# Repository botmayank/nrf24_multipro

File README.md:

# nrf24_multipro_h8_pc
nRF24L01 multi-protocol RC transmitter project being used for JJRC/Eachine H8 mini to control over Serial. This project aims to develop a USB dongle to control the H8 directly from the PC using the nRF24L01+ module and later expand to control and/or charge multiple quadcopters with this custom hardware based on the Arduino Leonardo (Atmega32u4).

The main Arduino code is in the nRF24_multipro folder with the main sketch being nRF24_multipro.ino. The script to control the quad over serial is serial_test.py while the board files for the Quadstick are in the hardware_design folder.

This project is based on the work of perrystao:
https://github.com/perrytsao/nrf24_cx10_pc

which in turn is based upon the awesome nrf24_multipro project by goebish:
https://github.com/goebish/nrf24_multipro

Arduino Nano and nRF24L01+ Module on perfboard to control Syma X20

## Connections

| Arduino Uno/Nano    | NRF24L01+ Module               | nRF Pin No.   |
|---------------------|--------------------------------|---------------|
| GND                 | GND                            | 1             |
| 3.3V                | VCC                            | 2             |
| D5 (Digital 5)      | CE                             | 3             |
| A1 (Analog 1)       | CSN                            | 4             |
| D4 (Digital 4)      | SCK                            | 5             |
| D3 (Digital 3)      | MOSI                           | 6             |
| A0 (Analog 0)       | MISO                           | 7             |
| Not Used            | IRQ                            | 8             |

# Configure

run `export PYTHONPATH=.` at the root of the project folder to run the files from terminal. 
Why this isn't needed on Pycharm is because it sets it for you.

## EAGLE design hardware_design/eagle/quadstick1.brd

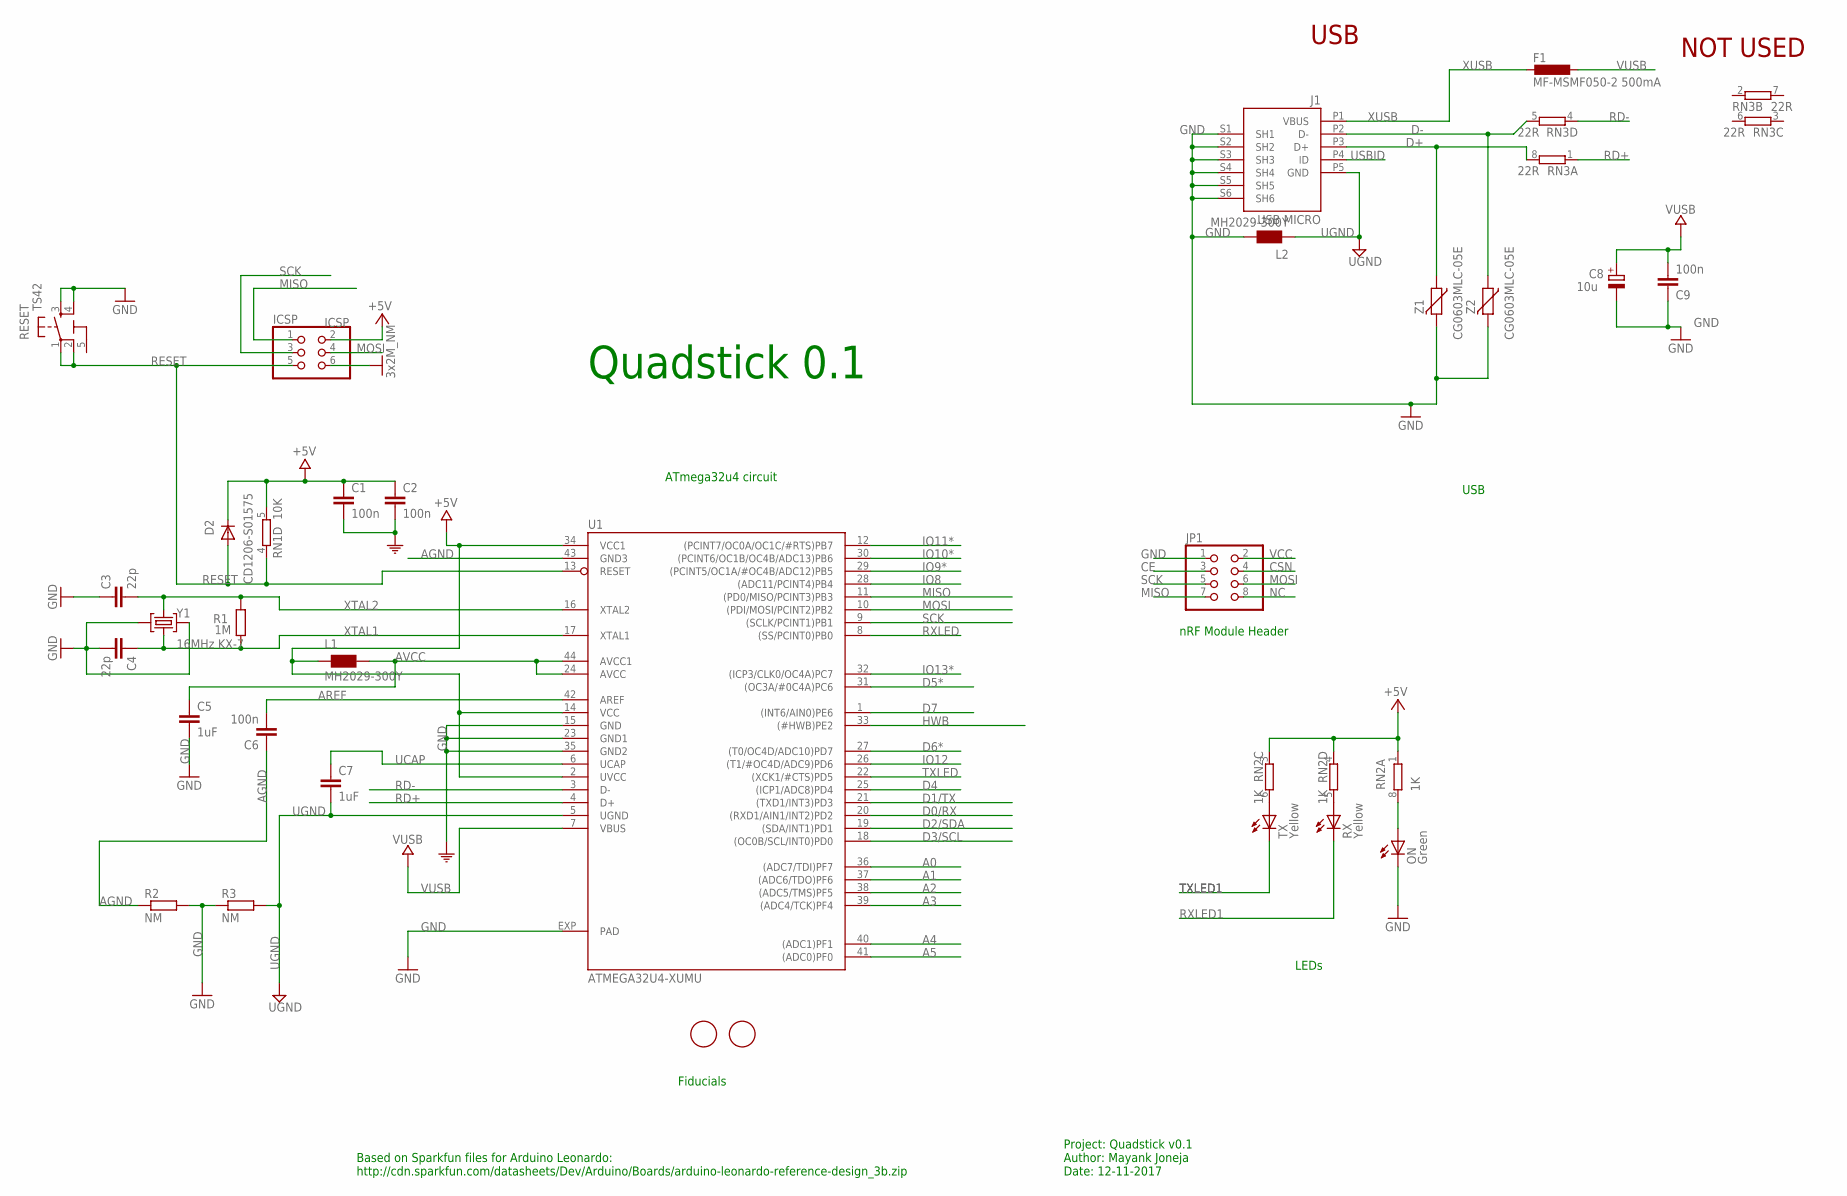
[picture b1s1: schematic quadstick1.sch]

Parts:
C1, C2, C6, C9: 100n; C0603-ROUND
C3, C4: 22p; C0603-ROUND
C5, C7: 1uF; C0603-ROUND
C8: 10u; SMC_B
D2: CD1206-S01575; MINIMELF
F1: MF-MSMF050-2 500mA; L1812
FID2, FID3: FIDUCIALMOUNT; FIDUCIA-MOUNT
ICSP: ICSP; 2X03
J1: USB MICRO; CON2_USB_MICRO_B_AT
JP1: PINHD-2X4; 2X04
L1, L2: MH2029-300Y; 0805
ON: Green; CHIPLED_0805
R1: 1M; R0603-ROUND
R2, R3: NM; R0402
RESET: TS42
RN1: 10K; CAY16
RN2: 1K; CAY16
RN3: 22R; CAY16
RX: Yellow; CHIPLED_0805
TX: Yellow; CHIPLED_0805
U1: ATMEGA32U4-XUMU; QFN44ML7X7
Y1: 16MHz KX-7; CRYSTAL-3.2-2.5
Z1, Z2: CG0603MLC-05E; CT/CN0603

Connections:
5-GND: RESET.5 (5-GND)
+5V: C1.1, C2.1, D2.C, ICSP.2, L1.1, RN1.5 (2), RN2.1, RN2.3 (1), RN2.4 (1), U1.2 (UVCC), U1.14 (VCC), U1.34 (VCC1)
A0: U1.36 ((ADC7/TDI)PF7)
A1: U1.37 ((ADC6/TDO)PF6)
A2: U1.38 ((ADC5/TMS)PF5)
A3: U1.39 ((ADC4/TCK)PF4)
A4: U1.40 ((ADC1)PF1)
A5: U1.41 ((ADC0)PF0)
AGND: C6.1, R2.1, U1.43 (GND3)
AREF: C6.2, U1.42 (AREF)
AVCC: C5.1, L1.2, U1.24 (AVCC), U1.44 (AVCC1)
CE: JP1.3
CSN: JP1.4
D0/RX: U1.20 ((RXD1/AIN1/INT2)PD2)
D1/TX: U1.21 ((TXD1/INT3)PD3)
D2/SDA: U1.19 ((SDA/INT1)PD1)
D3/SCL: U1.18 ((OC0B/SCL/INT0)PD0)
D4: U1.25 ((ICP1/ADC8)PD4)
D5*: U1.31 ((OC3A/#0C4A)PC6)
D6*: U1.27 ((T0/OC4D/ADC10)PD7)
D7: U1.1 ((INT6/AIN0)PE6)
D+: J1.P3 (D+), RN3.8 (2), Z1.1
D-: J1.P2 (D-), RN3.5 (2), Z2.1
GND: C1.2, C2.2, C3.1, C4.2, C5.2, C8.-, C9.1, ICSP.6, J1.S1 (SH1), J1.S2 (SH2), J1.S3 (SH3), J1.S4 (SH4), J1.S5 (SH5), J1.S6 (SH6), JP1.1, L2.2, ON.C, R2.2, R3.1, RESET.3, RESET.4, U1.15 (GND), U1.23 (GND1), U1.35 (GND2), U1.EXP (PAD), Y1.2 (GND), Y1.4 (GND), Z1.2, Z2.2
HWB: U1.33 ((#HWB)PE2)
IO8: U1.28 ((ADC11/PCINT4)PB4)
IO9*: U1.29 ((PCINT5/OC1A/#OC4B/ADC12)PB5)
IO10*: U1.30 ((PCINT6/OC1B/OC4B/ADC13)PB6)
IO11*: U1.12 ((PCINT7/OC0A/OC1C/#RTS)PB7)
IO12: U1.26 ((T1/#OC4D/ADC9)PD6)
IO13*: U1.32 ((ICP3/CLK0/OC4A)PC7)
MISO: ICSP.1, JP1.7, U1.11 ((PD0/MISO/PCINT3)PB3)
MOSI: ICSP.4, JP1.6, U1.10 ((PDI/MOSI/PCINT2)PB2)
unnamed: ON.A, RN2.8 (2)
unnamed: RN2.6 (2), TX.A
unnamed: RN2.5 (2), RX.A
NC: JP1.8
RD+: RN3.1, U1.4 (D+)
RD-: RN3.4 (1), U1.3 (D-)
RESET: D2.A, ICSP.5, RESET.1, RESET.2, RN1.4 (1), U1.13 (RESET)
RXLED: U1.8 ((SS/PCINT0)PB0)
RXLED1: RX.C
SCK: ICSP.3, JP1.5, U1.9 ((SCLK/PCINT1)PB1)
TXLED: U1.22 ((XCK1/#CTS)PD5)
TXLED1: TX.C
UCAP: C7.1, U1.6 (UCAP)
UGND: C7.2, J1.P5 (GND), L2.1, R3.2, U1.5 (UGND)
USBID: J1.P4 (ID)
VCC: JP1.2
VUSB: C8.+, C9.2, F1.1, U1.7 (VBUS)
XTAL1: C4.1, R1.1, U1.17 (XTAL1), Y1.1 (C1)
XTAL2: C3.2, R1.2, U1.16 (XTAL2), Y1.3 (C2)
XUSB: F1.2, J1.P1 (VBUS)

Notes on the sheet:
Project: Quadstick v0.1 Author: Mayank Joneja Date: 12-11-2017
USB
NOT USED
Based on Sparkfun files for Arduino Leonardo: http://cdn.sparkfun.com/datasheets/Dev/Arduino/Boards/arduino-leonardo-reference-design_3b.zip
Quadstick 0.1
nRF Module Header
LEDs
Fiducials
ATmega32u4 circuit

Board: 2 copper layers, 32 parts (0 on the bottom side), 22 nets, no tracks yet.

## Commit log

2017-11-10 Init working, bind not done
2017-11-14 Modification for h8 and serial python script
2017-11-14 Readme updated
2017-11-14 Eagle Schematic basic from Arduino Leonardo
2017-11-14 Added photo of setup
2017-11-25 Modified for Linux implementing msvcrt functions using sys calls
2017-11-25 arduino sketch moved to nrf24_multipro_h8
2017-11-25 Working modified perrytsao project for h8 mini
2018-01-03 added eagle layout
2018-01-10 Re-positioned all components for USB and Analog parts to top layer for easier reflow
2018-09-03 Added datasheets for quadstick
2018-09-03 Cleaned up main arduino script for Syma, JJRC H8 and H8 3D
2018-09-03 Changed serial port
2018-09-03 Updated README.md for Syma X20
2018-09-03 Correct relative jpg link in README.md
2018-09-03 Added .jpeg extensions
2018-09-08 rc_scripts for controlling using curses
2018-09-08 Throttle control added with special keys
2018-09-09 Added all controls roll, pitch, yaw
2018-09-09 Fixed pitch bug in update_input
2018-09-14 Update gitignore for python + intellij
2018-09-14 Decoupled keyboard input and flight controller
2018-09-14 Serial Syma cleanup
2018-09-14 Add aruco finder
    todo: add the camera calib package if there'll be one
2018-09-14 Add calibration script
    Write to yaml
2018-09-14 Add aruco generator helper
2018-09-14 Add capture images file
    Super surprised I don't find this written in python that I can take off
    the shelf
    Will later make a single camera open/close class
2018-09-14 Basic bang-bang controller for height
2018-09-14 Added optional delta args to exposed flight methods in SymaController
2018-09-14 Set physical dimension for aruco markers
2018-09-14 Added README for auto_flight
2018-09-15 Working throttle control
    There was a silly mistake in calculating the distance between the
    corners sigh. Should ideally use the tvec and rvec provided by
    estimatePose
    Still very primitive.
    The code's kinda messy right now - but we'll clean it up
2018-09-15 Integrate aruco finder into control
    todo - cap the max and min received from the aruco finder
2018-09-15 Add joystick controller using pygame
2018-09-15 Rename manual input to keyboard input
2018-09-15 Add commands for relative values of quad controls
    These will allow for exact values instead of changing using a gain or
    delta parameter
2018-09-15 Repackaging for better understanding of what we're doing
    - manual inputs using keyboard and joystick
    - autonomous inputs using camera
2018-09-15 Fly quad with joystick works
    figured out that setting roll pitch directly (range -1 ro 1) works a lot
    better than incrementing it as in the case of throttle. In that too, the
    max and min values don't exactly hold - figured out what their acromode
    effectively does; sends higher threshold of the RPY values.
    Throttle it only makes sense to be changing things with deltas.
    Also, keeping the quad stuck the rope kinda fucks it up.
2018-09-16 Add commands for shut down and start
2018-09-16 Add acro-mode using r1 and r2 for better control
    I think the RPY part is sorted; still not happy with the throttle
    though. It doesn't seem to stick to how much I ask it to - even though
    we're changing the throttle only using deltas. Steady state is probably
    a value lower than the one actually set
2018-09-16 Update aruco_finder to read from redmi calib + static video
    Todo, later will make this pick cameras and calibs properly, just
    hardcoding badly right now cuz I want to see results
2018-09-16 Show detection rate in aruco finder
2018-09-18 Try different aruco parameters
2018-09-20 Controller works perfectly + use a simple off the shelf tracker
    The opencv tracker works moderately well. Will use this atm.
    Except I used some shitty hardcoding there.
2018-09-20 Move camera things to camerasrc
2018-09-21 Draw proper bounding box on quad copter while tracking
2018-09-22 Draw yaw angle on the frame
2018-09-23 Add Pose class and use that to encapsulate tracking / detections
2018-09-23 Add initial try at center maintain
    This doesn't work as easyily as I thought it would.
    Realized I'll need a lot of black chart paper + make a controller and
    figure out what to do one by one
2018-09-23 Simple shield for nRF module and Arduino Nano in KiCAD
    (cherry picked from commit f9ca69a161c57fbc2aba25abcecc165ee3b5d1f5)
2018-09-23 Run aruco as a child process and pipe its output
    This is a very naive attempt but things seem to be shaping up.
    The detection rate is still low - mostly because the paper I'm using is
    shining. Another thing that I have to do is find the rotation based on
    tracked box
2018-09-24 Calculate yaw based on contour detection
    Basically needed to know yaw when the drone isn't detected by aruco
2018-09-28 Completed layout for nRF Dongle
